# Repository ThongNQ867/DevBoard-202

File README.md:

# DevBoard202
This is a dev board that runs with the RP2040 but structured more simple than Pi Pico. The schematic is inspired by the document "Hardware design with RP2040", the PCB is made with the tutorial from @KaiPereira.
The reason I do this project is to understand more about how capacitors, resistors are used with components like MCU, oscillator, USB ports. Moreover, design a development board provide more control over how  I can use the MCU, in which I remove some functionalities from the Pi Pico to make this board simple and easier to use. 

Using instruction:
Using this development board is similar to any other development board. We can just plug wires to GPIO pins to use. The usage of GPIO pins can be find on the datasheet of Raspberry Pi Pico or the RP2040 itself. This dev board can be used with external power source, and to do so, we can wire a 5V power source to the VBus or VSYS pins.

While there is a tutorial from Blueprint, I think it is better to fact check stuffs again and get understand more clearly about how to set up the value for resistors and capacitors by myself from these 2 links:
RP2040 datasheet
https://pip-assets.raspberrypi.com/categories/814-rp2040/documents/RP-008371-DS-1-rp2040-datasheet.pdf?disposition=inline

Hardware design with rp2040
https://pip-assets.raspberrypi.com/categories/814-rp2040/documents/RP-008279-DS-1-hardware-design-with-rp2040.pdf?disposition=inline

Pi Pico Datasheet
https://pip-assets.raspberrypi.com/categories/610-raspberry-pi-pico/documents/RP-008307-DS-1-pico-datasheet.pdf?disposition=inline

Here is the result:
3D model: 

Schematic: 

PCB: 

First, lets start of with setting up the decoupling capacitors. From the tutorial, it is recommended to used 1 capacitors per powerline so I just follow it. However, I found it a bit troublesome to actually know which pin is a powerline as I'm not very used to reading datasheets. Before this, I had always connect the pins to the capacitor (just as the datasheets often describe), making the schematic super hard to read. However, from the tutorial, I learnt that I can connect them seperately, making the schematic much more easier to read, and also solving the problem that the symbol of rp2040 on kicad doesnt shows all the power pins. 

Next is the powerline. Though it looks simple, it actually took me some time to actually figure out how the powerline, VSYS and VBUS works as I was trying to make my devboard be able to use an external power source. I added a VSYS pin which include the use of a Schottky diode between the VBUS and VSYS so that I can power it by an external power source. I found it quite challenging to understand how the USB host mode work but I think powering the external power source to the VBUS would probably be fine. Also because of powering externally to VSYS, I also pull VBUS down if its not connected to power source with 2 resistors to GND. After that, I also decided to wire the VBUS to a GPIO pin to detect if the board is using external power source

SPI flash, built-in LED and oscillator is pretty straight forward, but I did learn so much on how to calculate the resistor for the oscillator.

For me, PCB routing is the most problematic part of this project, partly because I'm new to KiCAD, partly because of the enormous diode (which I have changed to a more cost effective and 10 times smaller version). I started trying to make a PCB with the size of a Pi Pico but ended up increase the width to make the wiring easier 

This project has taught me a lot on how to use KiCAD and choose componets to print for my PCB. 

BOM: 
| Name                      | Comment | Designator                           | Footprint                                   | JLCPCB Part # | Quantity | Links |
|--------------------------|---------|-------------------------------------|--------------------------------------------|--------------|----------|-------|
| CL10A106MA8NRNC | 10uF | C15,C16 | C_0603_1608Metric | C96446 | 2 | https://jlcpcb.com/partdetail/97651-CL10A106MA8NRNC/C96446 |
| CL05A105KA5NQNC | 1uF | C9,C14 | C_0402_1005Metric | C52923 | 2 | https://jlcpcb.com/partdetail/53938-CL05A105KA5NQNC/C52923 |
| MCP1700T-3302E/TT LDO | MCP1700x-330xxTT | U2 | SOT-23 | C39051 | 1 | https://jlcpcb.com/partdetail/MicrochipTech-MCP1700T_3302ETT/C39051 |
| 0402CG330J500NT | 33pF | C18,C17 | C_0402_1005Metric | C1562 | 2 | https://jlcpcb.com/partdetail/1914-0402CG330J500NT/C1562 |
| 0402WGF1001TCE | 1k | R7,R5 | R_0402_1005Metric | C11702 | 2 | https://jlcpcb.com/partdetail/12256-0402WGF1001TCE/C11702 |
| RCT0227RJLF | 27 | R3,R4 | R_0402_1005Metric | C174257 | 2 | https://jlcpcb.com/partdetail/HKR_Hong_Kong_Resistors-RCT0227RJLF/C174257 |
| 0402WGF5101TCE | 5.1k | R2,R1 | R_0402_1005Metric | C25905 | 2 | https://jlcpcb.com/partdetail/26648-0402WGF5101TCE/C25905 |
| X322512MSB4SI oscillator | 12MHz | Y1 | Crystal_SMD_3225-4Pin_3.2x2.5mm | C9002 | 1 | https://jlcpcb.com/partdetail/YXC_CrystalOscillators-X322512MSB4SI/C9002 |
| 0402WGF5601TCE | 5k6 | R8 | R_0402_1005Metric | C25908 | 1 | https://jlcpcb.com/partdetail/26651-0402WGF5601TCE/C25908 |
| 1N4148WS diode | 1N4148WS | D1 | D_SOD-323 | C2128 | 1 | https://jlcpcb.com/partdetail/2485-1N4148WS/C2128 |
| 0402WGF470JTCE | 470 | R10 | R_0402_1005Metric | C25118 | 1 | https://jlcpcb.com/partdetail/25861-0402WGF470JTCE/C25118 |
| RP2040 | RP2040 | U1 | QFN-56-1EP_7x7mm_P0.4mm_EP3.2x3.2mm | C2040 | 1 | https://jlcpcb.com/partdetail/RaspberryPi-RP2040/C2040 |
| CL05B104KO5NNNC | 100nF | C8,C7,C13,C5,C12,C1,C2,C6,C4,C10,C3 | C_0402_1005Metric | C1525 | 11 | https://jlcpcb.com/partdetail/1877-CL05B104KO5NNNC/C1525 |
| W25Q16JVUXIQ Flash | W25Q16JVZPIQTR | U3 | Winbond_USON-8-1EP_3x2mm_P0.5mm_EP0.2x1.6mm | C2843335 | 1 | https://jlcpcb.com/partdetail/WinbondElec-W25Q16JVUXIQ/C2843335 |
| KT-0603R LED | LED | D2 | LED_0603_1608Metric | C2286 | 1 | https://jlcpcb.com/partdetail/Hubei_KENTOElec-KT0603R/C2286 |
| 402WGF1002TC | 10k | R6,R9 | R_0402_1005Metric | C25744 | 2 | https://jlcpcb.com/partdetail/26487-0402WGF1002TCE/C25744 |
| TYPE-C-31-M-12 USB-C port | USB_C_Receptacle_USB2.0_14P | J1 | USB_C_Receptacle_HRO_TYPE-C-31-M-12 | C165948 | 1 | https://jlcpcb.com/partdetail/Korean_HropartsElec-TYPE_C_31_M12/C165948 |
| TS-1088-AR02016 | SW_Push | SW1 | SW_Push_SPST_NO_Alps_SKRK | C720477 | 1 | https://jlcpcb.com/partdetail/XUNPU-TS_1088AR02016/C720477 |

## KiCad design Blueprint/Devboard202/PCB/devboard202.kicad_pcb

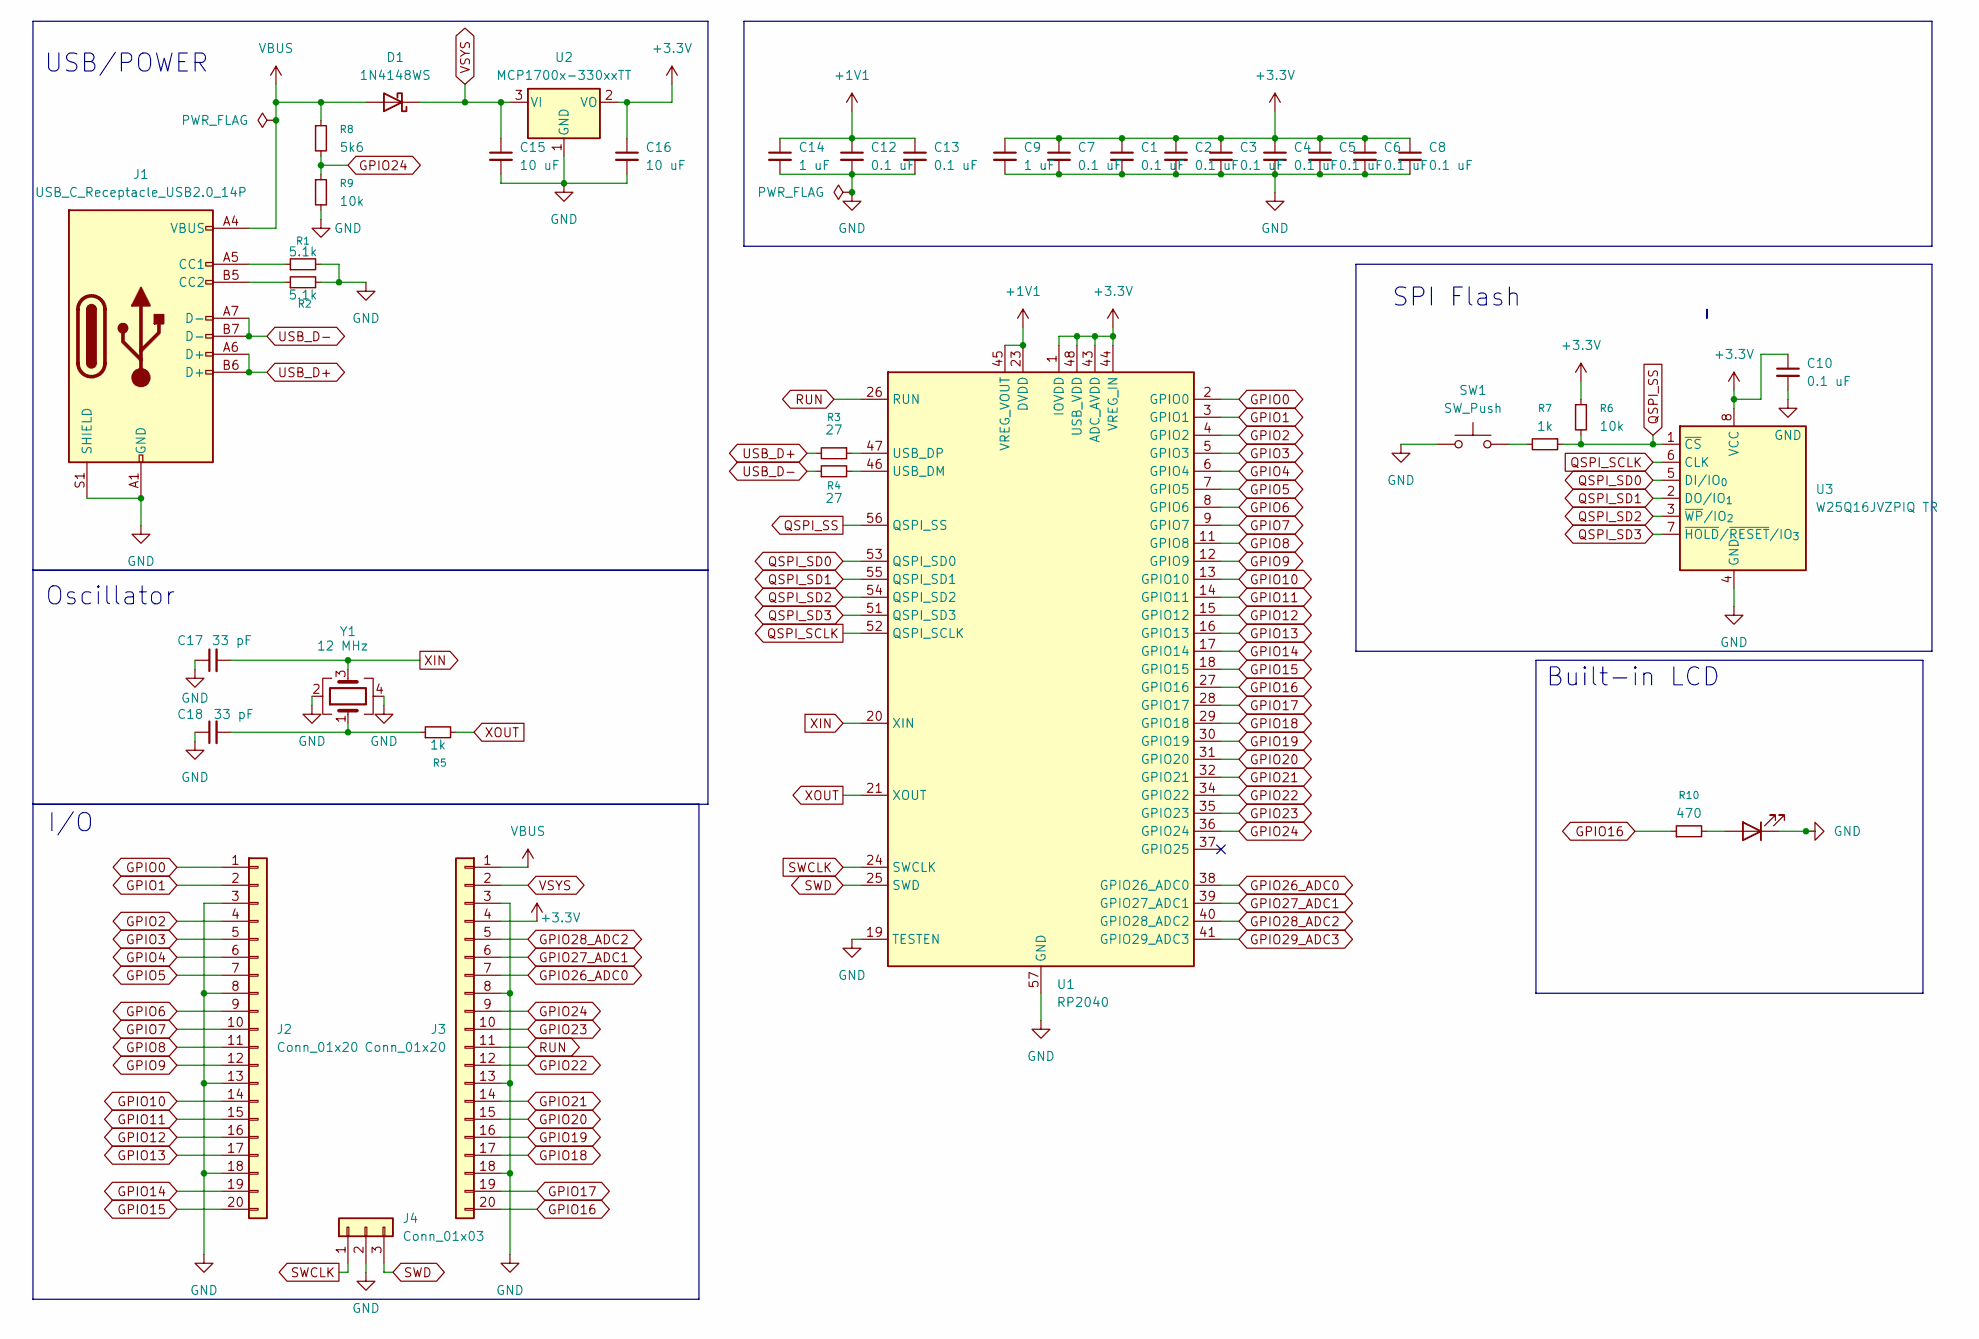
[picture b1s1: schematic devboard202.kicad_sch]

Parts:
C1, C2, C3, C4, C5, C6, C7, C8, C10, C12, C13: 0.1 uF; C_0402_1005Metric
C9, C14: 1 uF; C_0402_1005Metric
C15, C16: 10 uF; C_0603_1608Metric
C17, C18: 33 pF; C_0402_1005Metric
D1: 1N4148WS; D_SOD-323
D2: LED; LED_0402_1005Metric
J1: USB_C_Receptacle_USB2.0_14P; USB_C_Receptacle_HRO_TYPE-C-31-M-12
J2, J3: Conn_01x20; PinHeader_1x20_P2.54mm_Vertical
J4: Conn_01x03; PinHeader_1x03_P2.54mm_Vertical
R1, R2: 5.1k; R_0402_1005Metric
R3, R4: 27; R_0402_1005Metric
R5, R7: 1k; R_0402_1005Metric
R6, R9: 10k; R_0402_1005Metric
R8: 5k6; R_0402_1005Metric
R10: 470; R_0402_1005Metric
SW1: SW_Push; SW_Push_SPST_NO_Alps_SKRK
U1: RP2040; QFN-56-1EP_7x7mm_P0.4mm_EP3.2x3.2mm
U2: MCP1700x-330xxTT; SOT-23
U3: W25Q16JVZPIQ TR; Winbond_USON-8-1EP_3x2mm_P0.5mm_EP0.2x1.6mm
Y1: 12 MHz; Crystal_SMD_3225-4Pin_3.2x2.5mm

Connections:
+1V1: C12.1, C13.1, C14.1, U1.23 (DVDD), U1.45 (VREG_VOUT), U1.50 (DVDD)
+3.3V: C1.1, C2.1, C3.1, C4.1, C5.1, C6.1, C7.1, C8.1, C9.1, C10.1, C16.1, J3.4, R6.1, U1.1 (IOVDD), U1.10 (IOVDD), U1.22 (IOVDD), U1.33 (IOVDD), U1.42 (IOVDD), U1.43 (ADC_AVDD), U1.44 (VREG_IN), U1.48 (USB_VDD), U1.49 (IOVDD), U2.2 (VO), U3.8 (VCC)
GND: C1.2, C2.2, C3.2, C4.2, C5.2, C6.2, C7.2, C8.2, C9.2, C10.2, C12.2, C13.2, C14.2, C15.2, C16.2, C17.1, C18.1, D2.1 (K), J1.A1 (GND), J1.A12 (GND), J1.B1 (GND), J1.B12 (GND), J1.S1 (SHIELD), J2.3, J2.8, J2.13, J2.18, J3.3, J3.8, J3.13, J3.18, J4.2, R1.2, R2.2, R9.2, SW1.1, U1.19 (TESTEN), U1.57 (GND), U2.1 (GND), U3.4 (GND), Y1.2, Y1.4
GPIO0: J2.1, U1.2 (GPIO0)
GPIO1: J2.2, U1.3 (GPIO1)
GPIO2: J2.4, U1.4 (GPIO2)
GPIO3: J2.5, U1.5 (GPIO3)
GPIO4: J2.6, U1.6 (GPIO4)
GPIO5: J2.7, U1.7 (GPIO5)
GPIO6: J2.9, U1.8 (GPIO6)
GPIO7: J2.10, U1.9 (GPIO7)
GPIO8: J2.11, U1.11 (GPIO8)
GPIO9: J2.12, U1.12 (GPIO9)
GPIO10: J2.14, U1.13 (GPIO10)
GPIO11: J2.15, U1.14 (GPIO11)
GPIO12: J2.16, U1.15 (GPIO12)
GPIO13: J2.17, U1.16 (GPIO13)
GPIO14: J2.19, U1.17 (GPIO14)
GPIO15: J2.20, U1.18 (GPIO15)
GPIO16: J3.20, R10.1, U1.27 (GPIO16)
GPIO17: J3.19, U1.28 (GPIO17)
GPIO18: J3.17, U1.29 (GPIO18)
GPIO19: J3.16, U1.30 (GPIO19)
GPIO20: J3.15, U1.31 (GPIO20)
GPIO21: J3.14, U1.32 (GPIO21)
GPIO22: J3.12, U1.34 (GPIO22)
GPIO23: J3.10, U1.35 (GPIO23)
GPIO24: J3.9, R8.2, R9.1, U1.36 (GPIO24)
GPIO26_ADC0: J3.7, U1.38 (GPIO26_ADC0)
GPIO27_ADC1: J3.6, U1.39 (GPIO27_ADC1)
GPIO28_ADC2: J3.5, U1.40 (GPIO28_ADC2)
GPIO29_ADC3: U1.41 (GPIO29_ADC3)
unnamed: C18.2, R5.1, Y1.1
unnamed: D2.2 (A), R10.2
unnamed: J1.A5 (CC1), R1.1
unnamed: J1.B5 (CC2), R2.1
unnamed: R7.2, SW1.2
unnamed: R4.2, U1.46 (USB_DM)
unnamed: R3.1, U1.47 (USB_DP)
QSPI_SCLK: U1.52 (QSPI_SCLK), U3.6 (CLK)
QSPI_SD0: U1.53 (QSPI_SD0), U3.5 (DI/IO_{0})
QSPI_SD1: U1.55 (QSPI_SD1), U3.2 (DO/IO_{1})
QSPI_SD2: U1.54 (QSPI_SD2), U3.3 (~WP/IO_{2})
QSPI_SD3: U1.51 (QSPI_SD3), U3.7 (~HOLD/~RESET/IO_{3})
QSPI_SS: R6.2, R7.1, U1.56 (QSPI_SS), U3.1 (~CS)
RUN: J3.11, U1.26 (RUN)
SWCLK: J4.1, U1.24 (SWCLK)
SWD: J4.3, U1.25 (SWD)
USB_D+: J1.A6 (D+), J1.B6 (D+), R3.2
USB_D-: J1.A7 (D-), J1.B7 (D-), R4.1
VBUS: D1.2 (A), J1.A4 (VBUS), J1.A9 (VBUS), J1.B4 (VBUS), J1.B9 (VBUS), J3.1, R8.1
VSYS: C15.1, D1.1 (K), J3.2, U2.3 (VI)
XIN: C17.2, U1.20 (XIN), Y1.3
XOUT: R5.2, U1.21 (XOUT)

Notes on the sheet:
Oscillator
Built-in LCD
SPI Flash
USB/POWER
I/O

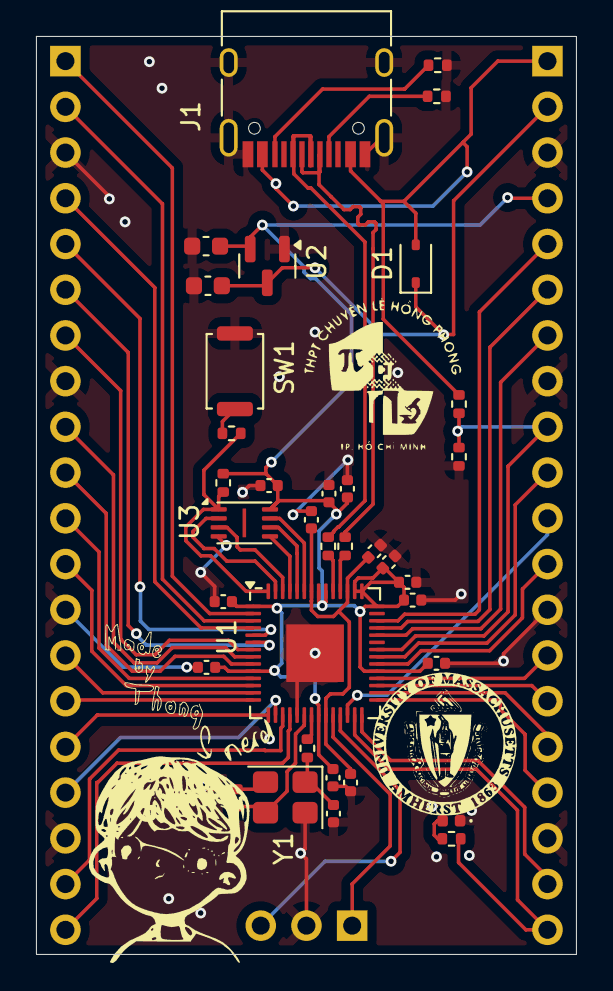
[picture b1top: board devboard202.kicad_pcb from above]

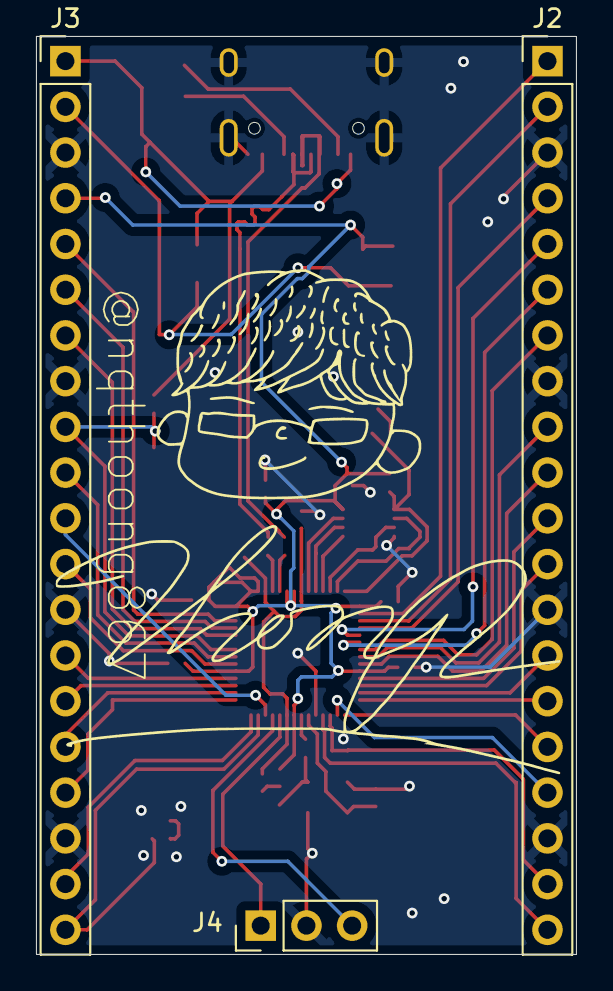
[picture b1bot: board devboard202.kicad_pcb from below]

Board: 2 copper layers, 30.0 x 51.0 mm, 38 parts (3 on the bottom side), 53 nets.

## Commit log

2026-01-20 Add README
2026-01-20 Update README
    Expanded project documentation with additional resources and insights on hardware design and PCB routing challenges.
2026-01-20 BOM Update
    Added a Bill of Materials (BOM) section
2026-02-02 update BOM
2026-02-02 update bom and .step file
2026-02-02 add BOM and .step file
2026-02-02 addlink for BOM
2026-02-20 Update the BOM
2026-02-20 gerber files update
2026-02-20 update images folder
2026-02-20 images update
2026-02-20 readme update
2026-02-20 organize the files
2026-03-12 student 2 part
